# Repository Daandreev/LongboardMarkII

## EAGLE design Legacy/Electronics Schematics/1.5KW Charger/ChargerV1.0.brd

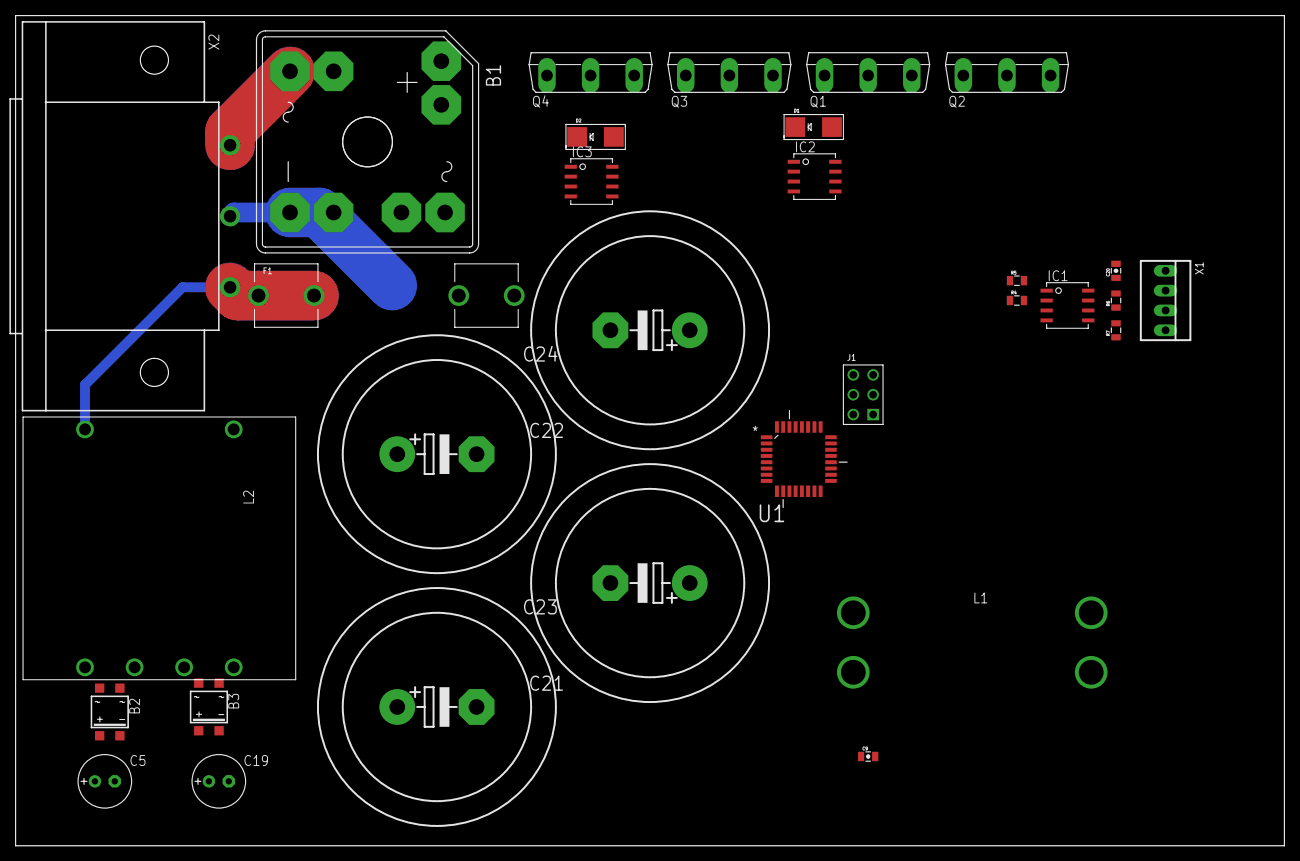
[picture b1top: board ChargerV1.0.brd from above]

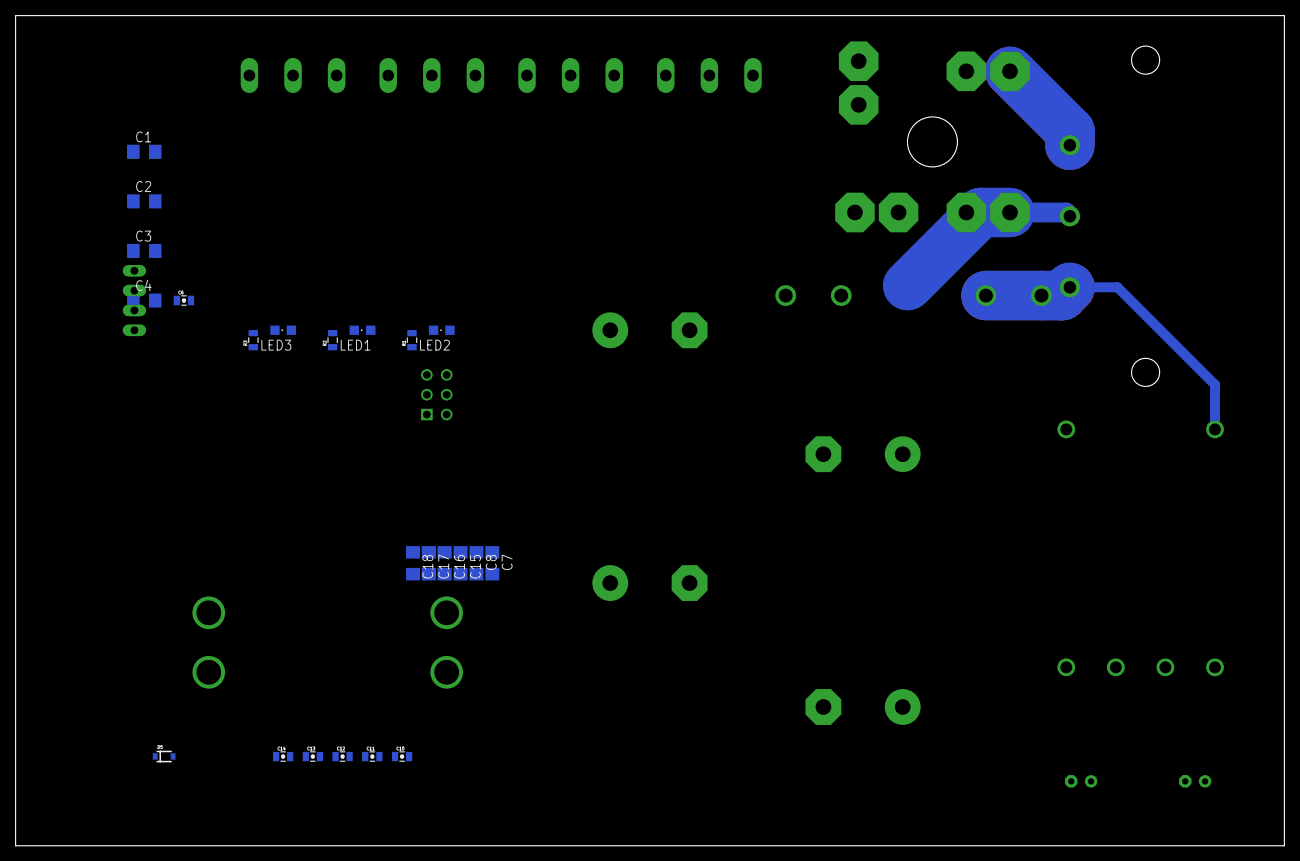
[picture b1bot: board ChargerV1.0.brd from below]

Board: 2 copper layers, 162.5 x 106.3 mm, 54 parts (23 on the bottom side), 37 nets.

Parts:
B1: B25A-
B2, B3: MB1S; SOIC-4
C1, C2, C7, C8, C15, C16, C17, C18: .47uF; C1206
C3, C4: .1uF; C1206
C5, C19: E2,5-7
C6, C20: .1uF; 0805-CAP
C9, C13, C14: 1uF; 0805-CAP
C10: 10uF; 0805-CAP
C11, C12: 0.1uF; 0805-CAP
C21: 2200uF; EB30D
C22, C23, C24: EB30D
D1, D2: SMADIODE
D5: 5.1V; SOD-323
F1: FUSE_HOLDER
IC1: SI8600_DUALCHANNELISO; SOIC-8
IC2, IC3: FAN7190; SOIC-8
J1: ISPHEADER; 2X3PIN_.1'
L1: 5:1; TRANSFORMER_TOR_CUSTOM
L2: 24:1:1; TRANSFORMER_CUSTOM1
LED1, LED2, LED3: CHIPLED_0805
Q1, Q2, Q3, Q4: FDA69N25; TO247BV
R1, R2, R3: 1k; 0805
R4, R5, R6, R7: 10k; 0805
U1: ATMEGA328P-AU; QFP80P900X900X120-32N
X1: 22-23-2041
X2: 6ESRM-P

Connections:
5V: B3.+, C6.1, C9.1, C10.1, C11.1, C12.2, C13.2, C14.1, C19.+, D5.C, IC1.P$1, J1.P$2, R4.2, R5.2, U1.4, U1.6, U1.18
5V_SEC: B2.+, C5.+, C20.1, IC1.P$8, R6.2, R7.2, X1.1
ACRECT: B1.+1, C21.+, C22.+, C23.+, C24.+, Q1.D, Q3.D
GND: B1.-1, B3.-, C6.2, C9.2, C10.2, C11.2, C12.1, C13.1, C14.2, C19.-, C21.-, C22.-, C23.-, C24.-, D1.A, D2.A, D5.A, IC1.P$4, IC2.P$3, IC2.P$5, IC3.P$3, IC3.P$5, J1.P$6, LED1.C, LED2.C, LED3.C, Q2.S, Q4.S, U1.3, U1.5, U1.21, X2.2
GND_SEC: B2.-, C5.-, C20.2, IC1.P$5, X1.4
HO1: IC2.P$7, Q1.G
HO2: IC3.P$7, Q3.G
HSO: C1.2, C3.2, C7.1, C8.1, C15.1, C16.1, C17.1, C18.1, IC2.P$6, Q3.S, Q4.D
IN_HO1: IC2.P$2, IC3.P$1, U1.9
IN_HO2: IC2.P$1, IC3.P$2, U1.10
LEDG: R1.1, U1.30
LEDR: R3.1, U1.32
LEDY: R2.1, U1.31
LO1: IC2.P$4, Q2.G
LO2: IC3.P$4, Q4.G
LSO: C2.2, C4.2, IC3.P$6, L1.P$2, Q1.S, Q2.D
MISO: J1.P$1, U1.16
MOSI: J1.P$4, U1.15
unnamed: F1.P$1, F1.P$2, L2.IN2, X2.3
unnamed: B1.AC1-, F1.P$3, F1.P$4
unnamed: B1.AC2-, L2.IN1, X2.1
unnamed: B3.~1, L2.OUT11
unnamed: B3.~2, L2.OUT12
unnamed: B2.~1, L2.OUT21
unnamed: B2.~2, L2.OUT22
unnamed: LED2.A, R1.2
unnamed: LED1.A, R2.2
unnamed: C1.1, C3.1, D1.C, IC2.P$8
unnamed: C2.1, C4.1, D2.C, IC3.P$8
unnamed: LED3.A, R3.2
unnamed: C7.2, C8.2, C15.2, C16.2, C17.2, C18.2, L1.P$1
RESET: J1.P$5, U1.29
SCK: J1.P$3, U1.17
SCL: IC1.P$3, R5.1, U1.28
SCL_SEC: IC1.P$6, R7.1, X1.3
SDA: IC1.P$2, R4.1, U1.27
SDA_SEC: IC1.P$7, R6.1, X1.2

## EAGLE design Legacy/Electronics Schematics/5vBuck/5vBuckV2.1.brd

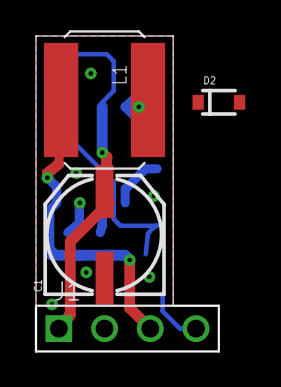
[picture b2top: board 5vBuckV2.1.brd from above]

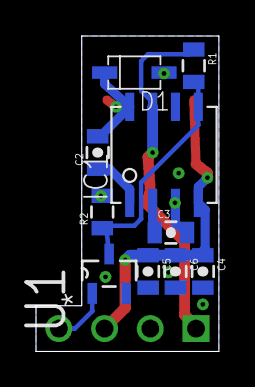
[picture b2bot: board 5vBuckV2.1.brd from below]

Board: 2 copper layers, 10.2 x 17.5 mm, 14 parts (10 on the bottom side), 8 nets.

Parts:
C1: 10uF; NIPPON_F80
C2, C3: 0.1uF; 0805-CAP
C4, C5: 22uF; 0805-CAP
C6: 1uF; 0805-CAP
D1: DIODE_SCHOTTKYSOD-123; SOD-123
D2: 5.6V; SOD-323
IC1: SOIC-8
J1: CONNECTOR_4PIN; 4PIN_.1'
L1: 220uH; 6X6MM_IND
R1: 680k; 0805
R2: 220k; 0805
U1: BSS138P; SOT95P230X110-3N

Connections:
GND: C1.-, C3.2, C4.2, C5.2, C6.2, D1.ANODE, D2.A, IC1.P$3, IC1.P$6, J1.P$2, R2.2, U1.2
IO: IC1.P$5, R1.2, R2.1, U1.3
unnamed: C2.2, D1.CATHODE, IC1.P$8, L1.P$1
unnamed: C2.1, IC1.P$1
unnamed: C3.1, IC1.P$2
SHDN: J1.P$4, U1.1
VIN: C1.+, IC1.P$7, J1.P$1, R1.1
VOUT: C4.1, C5.1, C6.1, D2.C, IC1.P$4, J1.P$3, L1.P$2

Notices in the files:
parts and their libraries:
SparkFun-Capacitors: Licensing: Creative Commons ShareAlike 4.0 International - https://creativecommons.org/licenses/by-sa/4.0
